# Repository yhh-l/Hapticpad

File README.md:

> Chinese V1-CN-1.8 chord firmware + Mac/Windows local toolbox: [Downloads](https://github.com/yhh-l/Hapticpad/releases/tag/v1-cn-1.8) · [中文说明](Software/Chinese-V1-1.8/使用说明.md). Host-verified; hardware acceptance pending. Existing firmware directories are preserved.

# CNCDan - Haptic Pad

[中文复刻、国内采购与 3D 打印说明](README_CN.md)

> This repository is a fork/reproduction of the original [dmcke5/Hapticpad](https://github.com/dmcke5/Hapticpad) project. Original mechanical, PCB and software designs belong to dmcke5 / CNCDan and remain under the original `CERN-OHL-S-2.0` license.

A 6 button macropad with a display for button labels and a mouse knob with haptic feedback!

[Project Video Link](https://youtu.be/bNUKRJQjuvQ)

#### Features

- 6 programmable macro buttons
- 128x64 OLED display for button labels and icons
- Support for up to 256 profiles for a total of 1536 macros
- Easy XML configuration, no special drivers required
- Macro button combinations can be configured with up to 3 simultaneous buttons or 3 separate button presses with configurable delays between them
- Micro SD storage for button labels and config files
- Haptic feedback mouse wheel with three different modes: Clicky, Twist and Momentum
- RGB ring with configurable colours and 5 different display modes: Halo, Bands, Breath, Rainbow, Solid and Off
- Easy profile switching with up/down profile buttons or profile list display
- The last profile is stored on the SD card, so the macro pad starts on the profile that was last active

#### Bill of Materials

The list below reflects the parts selected for this fork/build. Links point to the exact part or the closest stable manufacturer/distributor page available.

- 1x [Waveshare 2.42-inch 128x64 OLED display](https://www.waveshare.com/product/ai/2.42inch-oled-module.htm)
- 1x 12 mm version of the [MT6701 magnetic encoder module](https://www.aliexpress.com/item/1005007469177411.html), configured for ABZ incremental output at 1024 PPR
  - Use the encoder's dedicated diametrically/radially magnetized magnet. The 6x1mm magnets below are only for the wheel coupling.
- 1x [2804 100KV brushless gimbal motor](https://www.aliexpress.com/item/1005006008489660.html) with a hollow shaft
- 6x [Kailh Choc V1 low-profile switches](https://www.aliexpress.com/item/1005005066585322.html)
- 1x [Waveshare RP2040-Plus](https://docs.waveshare.com/RP2040-Plus), 16MB without pre-soldered headers (SKU 23503)
- 1x [SparkFun TMC6300 3-phase motor driver board, ROB-21867](https://www.sparkfun.com/sparkfun-brushless-motor-driver-3-phase-tmc6300.html)
- 1x [Micro SD module](https://www.aliexpress.com/item/1005010587984346.html)
  - A FAT32-formatted Micro SD card is also required; this build already has one.
- 4x [6x1mm magnets](https://www.aliexpress.com/item/1005009894772141.html)
- 2x [Panasonic EVQ-Q2K03W tactile buttons](https://www.digikey.com/en/products/detail/panasonic-electronic-components/EVQ-Q2K03W/762893)
  - The original BOM specifies EVQ-Q2B03W. Check installed height and mechanical fit before final assembly.
- 1x [10nF / 50V / 0603 / 103 X7R capacitor, LCSC C307346](https://www.lcsc.com/search?q=C307346) for controller-board C1

The following parts are optional if you want to include the LEDs:

- 20x [Worldsemi WS2812B-B/W, 5050 / PLCC4, LCSC C114586](https://www.lcsc.com/zh-TW/product-detail/RGB-LEDs_Worldsemi-WS2812B-B-W_C114586.html)
  - Do not use the WS2812B 2020 package; it does not match the PCB footprint. On this PCB with the selected 5050 LED, the LED cut corner is diagonally opposite the PCB `1` marking. See the [illustrated orientation guide](README_CN.md).
- 20x [0.1uF (100nF) 0603 capacitors](https://www.aliexpress.com/item/32966526545.html)

#### Hardware

- 9x [M3x5x5 threaded inserts](https://www.aliexpress.com/w/wholesale-m3x5x5-threaded-insert.html) (only needed for the printed housing)
- 3x [M3x6 socket-head cap screws](https://www.aliexpress.com/w/wholesale-m3x6-socket-head-screw.html)
- 2x [M3x10 socket-head cap screws](https://www.aliexpress.com/w/wholesale-m3x10-socket-head-screw.html)
- 10x [M2.5x4 socket-head cap screws](https://www.aliexpress.com/w/wholesale-m2.5x4-socket-head-screw.html)
- 4x [M2x6 countersunk screws](https://www.aliexpress.com/w/wholesale-m2x6-countersunk-screw.html) (the original README incorrectly listed M3x6; these are separate from the encoder screws)
- M2.5x4 screws for the display, M2.5x6 screws for the motor, and M2x4 screws for the 12 mm encoder module in this build; confirm counts and head styles against the physical mounting holes before ordering.
- 2 small ring washers; verify size, material, and mounting location on the physical build. Do not conflate these with the two printed `PCB Spacer.STL` parts.

### Printing Instructions

#### Printed version

Print all files in the `3D Files/STL's` folder. You will need 6 of the keycap file, 2 of the Menu button file and 2 of the PCB spacer file.

> [!WARNING]
> Uploading `Macro Pad - Printed Version.STL` may trigger a thin-wall warning for the main housing because the LED support features are too thin. Do not ignore the warning blindly: request a manual engineering review or thicken the LED supports before printing. If you print the file as-is, inspect the supports carefully and avoid applying force while fitting the LEDs.

#### Machined version

Print all files in the `3D Files/STL's` folder except `Custom Keycap.STL`, `Macro Pad - Printed Version.STL` and `Menu Button Printed.STL`.

Get all of the `.STEP` files in the `3D Files/STEP` folder machined. Do not include the Macropad Assembly `.STEP` file from the main directory, as it is a complete model of the Macro Pad rather than an individual part. If you supply the `MacroPad Housing.PDF` file with the housing, you can have the mounting holes tapped for you.

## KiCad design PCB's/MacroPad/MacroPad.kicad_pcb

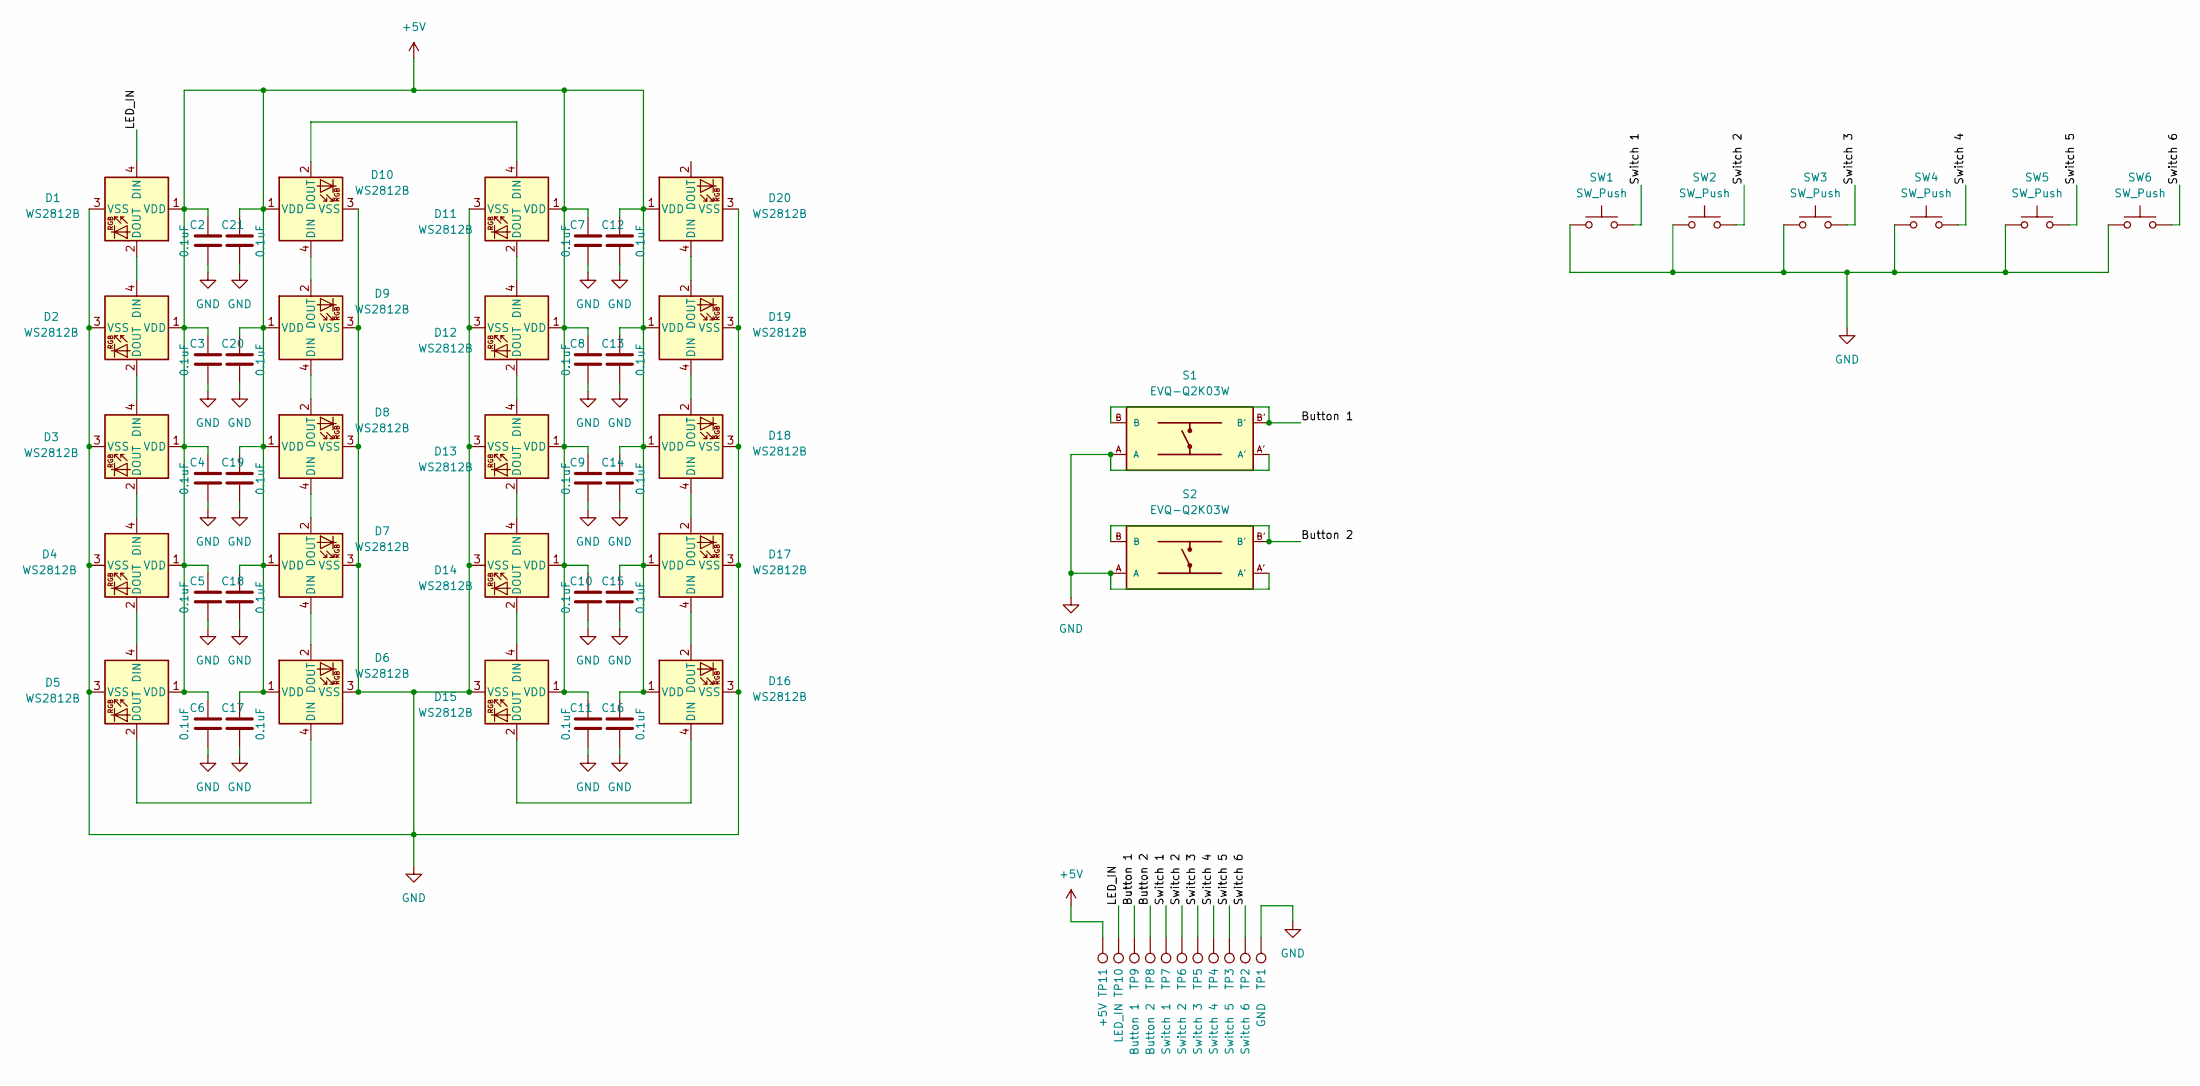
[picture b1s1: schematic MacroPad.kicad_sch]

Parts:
C2, C3, C4, C5, C6, C7, C8, C9, C10, C11, C12, C13, C14, C15, C16, C17, C18, C19, C20, C21: 0.1uF; C_0603_1608Metric
D1, D2, D3, D4, D5, D6, D7, D8, D9, D10, D11, D12, D13, D14, D15, D16, D17, D18, D19, D20: WS2812B; LED_WS2812B_PLCC4_5.0x5.0mm_P3.2mm
S1, S2: EVQ-Q2K03W; SW_EVQ-Q2B02W
SW1, SW2, SW3, SW4, SW5, SW6: SW_Push; SW_PG1350_reversible
TP1: GND; TestPoint_THTPad_D1.0mm_Drill0.5mm
TP2: Switch 6; TestPoint_THTPad_D1.0mm_Drill0.5mm
TP3: Switch 5; TestPoint_THTPad_D1.0mm_Drill0.5mm
TP4: Switch 4; TestPoint_THTPad_D1.0mm_Drill0.5mm
TP5: Switch 3; TestPoint_THTPad_D1.0mm_Drill0.5mm
TP6: Switch 2; TestPoint_THTPad_D1.0mm_Drill0.5mm
TP7: Switch 1; TestPoint_THTPad_D1.0mm_Drill0.5mm
TP8: Button 2; TestPoint_THTPad_D1.0mm_Drill0.5mm
TP9: Button 1; TestPoint_THTPad_D1.0mm_Drill0.5mm
TP10: LED_IN; TestPoint_THTPad_D1.0mm_Drill0.5mm
TP11: +5V; TestPoint_THTPad_D1.0mm_Drill0.5mm

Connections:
+5V: C2.1, C3.1, C4.1, C5.1, C6.1, C7.1, C8.1, C9.1, C10.1, C11.1, C12.1, C13.1, C14.1, C15.1, C16.1, C17.1, C18.1, C19.1, C20.1, C21.1, D1.1 (VDD), D2.1 (VDD), D3.1 (VDD), D4.1 (VDD), D5.1 (VDD), D6.1 (VDD), D7.1 (VDD), D8.1 (VDD), D9.1 (VDD), D10.1 (VDD), D11.1 (VDD), D12.1 (VDD), D13.1 (VDD), D14.1 (VDD), D15.1 (VDD), D16.1 (VDD), D17.1 (VDD), D18.1 (VDD), D19.1 (VDD), D20.1 (VDD), TP11.1
/Button 1: S1.B, S1.B', TP9.1
/Button 2: S2.B, S2.B', TP8.1
/LED_IN: D1.4 (DIN), TP10.1
/Switch 1: SW1.2, TP7.1
/Switch 2: SW2.2, TP6.1
/Switch 3: SW3.2, TP5.1
/Switch 4: SW4.2, TP4.1
/Switch 5: SW5.2, TP3.1
/Switch 6: SW6.2, TP2.1
GND: C2.2, C3.2, C4.2, C5.2, C6.2, C7.2, C8.2, C9.2, C10.2, C11.2, C12.2, C13.2, C14.2, C15.2, C16.2, C17.2, C18.2, C19.2, C20.2, C21.2, D1.3 (VSS), D2.3 (VSS), D3.3 (VSS), D4.3 (VSS), D5.3 (VSS), D6.3 (VSS), D7.3 (VSS), D8.3 (VSS), D9.3 (VSS), D10.3 (VSS), D11.3 (VSS), D12.3 (VSS), D13.3 (VSS), D14.3 (VSS), D15.3 (VSS), D16.3 (VSS), D17.3 (VSS), D18.3 (VSS), D19.3 (VSS), D20.3 (VSS), S1.A, S1.A', S2.A, S2.A', SW1.1, SW2.1, SW3.1, SW4.1, SW5.1, SW6.1, TP1.1
unnamed: D1.2 (DOUT), D2.4 (DIN)
unnamed: D2.2 (DOUT), D3.4 (DIN)
unnamed: D3.2 (DOUT), D4.4 (DIN)
unnamed: D4.2 (DOUT), D5.4 (DIN)
unnamed: D5.2 (DOUT), D6.4 (DIN)
unnamed: D6.2 (DOUT), D7.4 (DIN)
unnamed: D7.2 (DOUT), D8.4 (DIN)
unnamed: D8.2 (DOUT), D9.4 (DIN)
unnamed: D9.2 (DOUT), D10.4 (DIN)
unnamed: D10.2 (DOUT), D11.4 (DIN)
unnamed: D11.2 (DOUT), D12.4 (DIN)
unnamed: D12.2 (DOUT), D13.4 (DIN)
unnamed: D13.2 (DOUT), D14.4 (DIN)
unnamed: D14.2 (DOUT), D15.4 (DIN)
unnamed: D15.2 (DOUT), D16.4 (DIN)
unnamed: D16.2 (DOUT), D17.4 (DIN)
unnamed: D17.2 (DOUT), D18.4 (DIN)
unnamed: D18.2 (DOUT), D19.4 (DIN)
unnamed: D19.2 (DOUT), D20.4 (DIN)

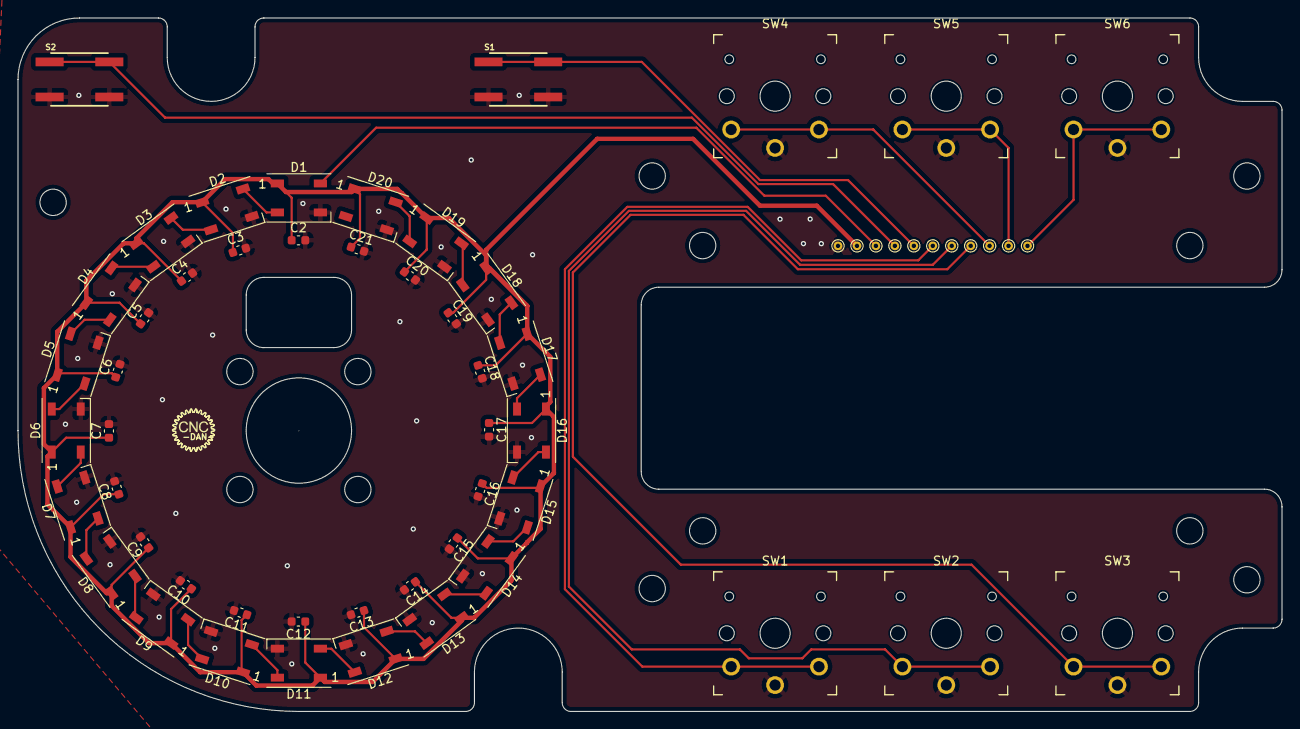
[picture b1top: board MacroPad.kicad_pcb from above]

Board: 2 copper layers, 144.0 x 79.0 mm, 59 parts (0 on the bottom side), 30 nets.
